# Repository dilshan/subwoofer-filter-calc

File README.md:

# Subwoofer bandpass filter calculator

Calculator application is a part of the *[active subwoofer filter system](http://jayakody2000lk.blogspot.com/2021/09/active-subwoofer-filter-circuit.html)*. This *active subwoofer filter system* provides the frequency required to run the subwoofer within its limits. The purpose of this unit is to prevent the subwoofer speaker or circuit from overloading at unsupported frequencies. 

This Calculator application is hosted on *GitHub Pages* and accessible at [dilshan.github.io/subwoofer-filter-calc](https://dilshan.github.io/subwoofer-filter-calc).

This repository contains the source code and design files of the calculator.

All the content of this project is released under the terms of the [MIT License](https://github.com/dilshan/subwoofer-filter-calc/blob/main/LICENSE).

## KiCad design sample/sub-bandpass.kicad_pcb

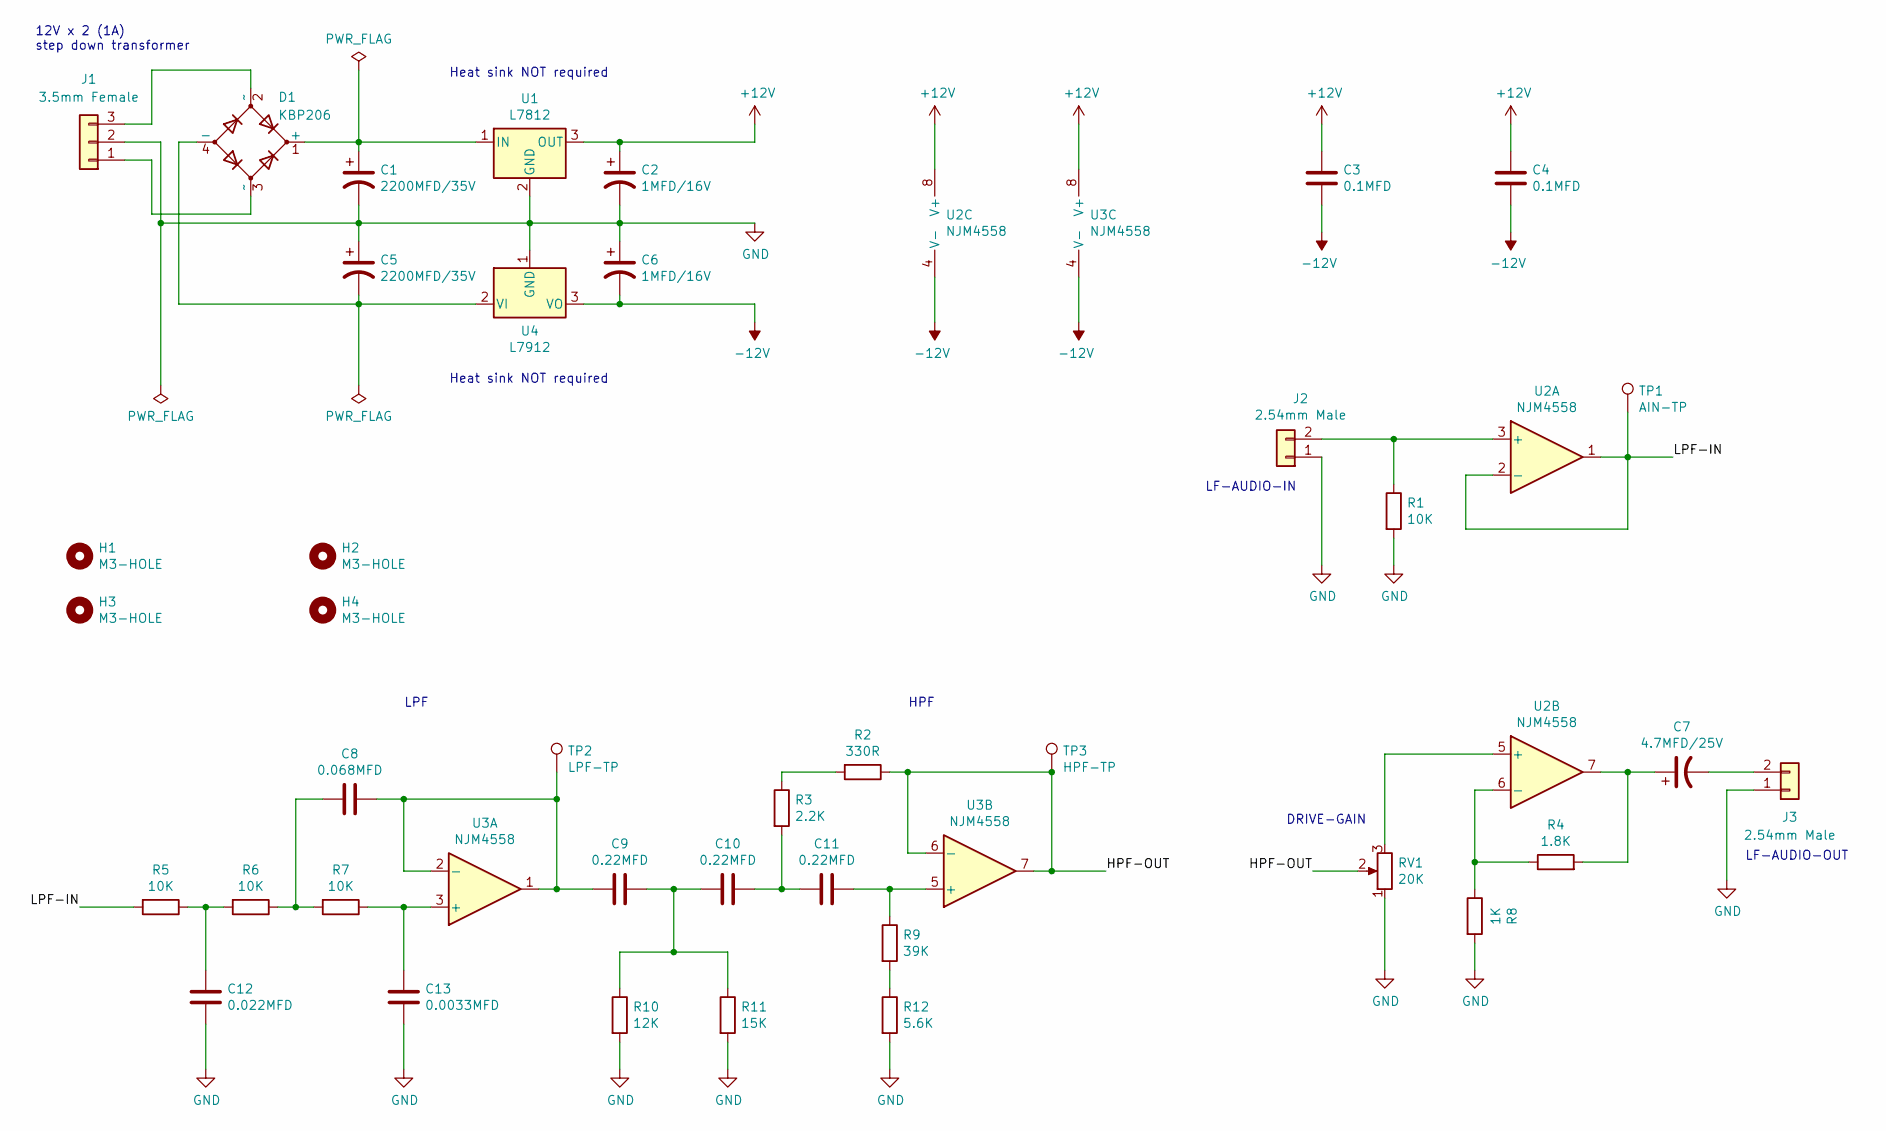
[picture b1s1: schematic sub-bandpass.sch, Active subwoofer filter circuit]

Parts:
C1, C5: 2200MFD/35V; CP_Radial_D22.0mm_P10.00mm_SnapIn
C2, C6: 1MFD/16V; CP_Radial_D5.0mm_P2.50mm
C3, C4: 0.1MFD; C_Rect_L9.0mm_W4.2mm_P7.50mm_MKT
C7: 4.7MFD/25V; CP_Radial_D5.0mm_P2.50mm
C8: 0.068MFD; C_Rect_L9.0mm_W4.0mm_P7.50mm_MKT
C9, C10, C11: 0.22MFD; C_Rect_L11.0mm_W4.2mm_P10.00mm_MKT
C12: 0.022MFD; C_Rect_L7.0mm_W3.5mm_P5.00mm
C13: 0.0033MFD; C_Disc_D6.0mm_W4.4mm_P5.00mm
D1: KBP206; Diode_Bridge_Vishay_KBPM
H1, H2, H3, H4: M3-HOLE; MountingHole_3.2mm_M3
J1: 3.5mm Female; PhoenixContact_MCV_1,5_3-G-3.5_1x03_P3.50mm_Vertical
J2, J3: 2.54mm Male; PinHeader_1x02_P2.54mm_Vertical
R1, R5, R6, R7: 10K; R_Axial_DIN0207_L6.3mm_D2.5mm_P10.16mm_Horizontal
R2: 330R; R_Axial_DIN0207_L6.3mm_D2.5mm_P10.16mm_Horizontal
R3: 2.2K; R_Axial_DIN0207_L6.3mm_D2.5mm_P10.16mm_Horizontal
R4: 1.8K; R_Axial_DIN0207_L6.3mm_D2.5mm_P10.16mm_Horizontal
R8: 1K; R_Axial_DIN0207_L6.3mm_D2.5mm_P10.16mm_Horizontal
R9: 39K; R_Axial_DIN0207_L6.3mm_D2.5mm_P10.16mm_Horizontal
R10: 12K; R_Axial_DIN0207_L6.3mm_D2.5mm_P10.16mm_Horizontal
R11: 15K; R_Axial_DIN0207_L6.3mm_D2.5mm_P10.16mm_Horizontal
R12: 5.6K; R_Axial_DIN0207_L6.3mm_D2.5mm_P10.16mm_Horizontal
RV1: 20K; Potentiometer_Runtron_RM-065_Vertical
TP1: AIN-TP; TestPoint_THTPad_1.5x1.5mm_Drill0.7mm
TP2: LPF-TP; TestPoint_THTPad_1.5x1.5mm_Drill0.7mm
TP3: HPF-TP; TestPoint_THTPad_1.5x1.5mm_Drill0.7mm
U1: L7812; TO-220-3_Vertical
U2, U3: NJM4558; DIP-8_W7.62mm_LongPads
U4: L7912; TO-220-3_Vertical

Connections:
+12V: C2.1, C3.1, C4.1, U1.3 (OUT), U2.8 (V+), U3.8 (V+)
-12V: C3.2, C4.2, C6.2, U2.4 (V-), U3.4 (V-), U4.3 (VO)
/HPF-OUT: R2.1, RV1.2, TP3.1, U3.6 (-), U3.7
/LPF-IN: R5.2, TP1.1, U2.1, U2.2 (-)
GND: C1.2, C2.2, C5.1, C6.1, C12.1, C13.1, J1.2, J2.1, J3.1, R1.2, R8.2, R10.2, R11.2, R12.2, RV1.1, U1.2 (GND), U4.1 (GND)
unnamed: C1.1, D1.1 (+), U1.1 (IN)
unnamed: C5.2, D1.4 (-), U4.2 (VI)
unnamed: C7.1, R4.2, U2.7
unnamed: C7.2, J3.2
unnamed: C8.1, C9.2, TP2.1, U3.1, U3.2 (-)
unnamed: C8.2, R6.1, R7.2
unnamed: C10.1, C11.2, R3.2
unnamed: C9.1, C10.2, R10.1, R11.1
unnamed: C11.1, R9.1, U3.5 (+)
unnamed: C12.2, R5.1, R6.2
unnamed: C13.2, R7.1, U3.3 (+)
unnamed: D1.2 (~~), J1.3
unnamed: D1.3 (~~), J1.1
unnamed: J2.2, R1.1, U2.3 (+)
unnamed: R2.2, R3.1
unnamed: R4.1, R8.1, U2.6 (-)
unnamed: R9.2, R12.1
unnamed: RV1.3, U2.5 (+)

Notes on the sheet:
12V x 2 (1A) step down transformer
Heat sink NOT required
HPF
LPF
DRIVE-GAIN
LF-AUDIO-IN
LF-AUDIO-OUT

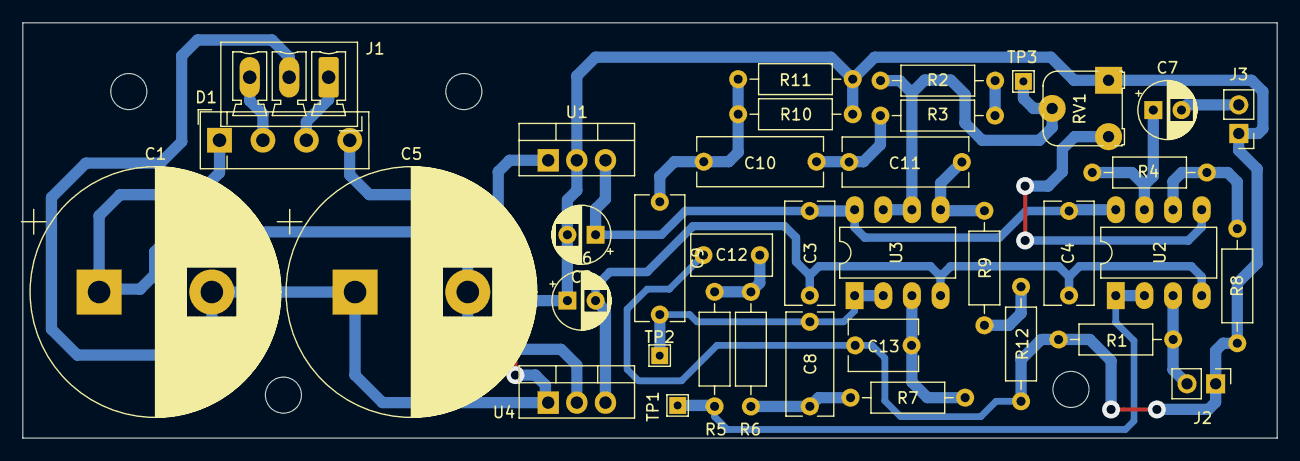
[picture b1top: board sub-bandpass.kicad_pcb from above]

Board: 2 copper layers, 111.3 x 36.8 mm, 41 parts (0 on the bottom side), 23 nets.

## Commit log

2021-09-18 Add initial version of filter calculator.
2021-09-18 Rename index.html to index.htm to fix page loading issues.
2021-09-18 Update folk URL in the index.htm page.
2021-09-19 Add initial version of readme.md file.
2021-09-20 Add sample project and preview schematic project.
2021-09-20 Add link to the project article at blogspot.com.
2021-09-20 Add link to the project article at blogspot.com. [to index.htm file]
